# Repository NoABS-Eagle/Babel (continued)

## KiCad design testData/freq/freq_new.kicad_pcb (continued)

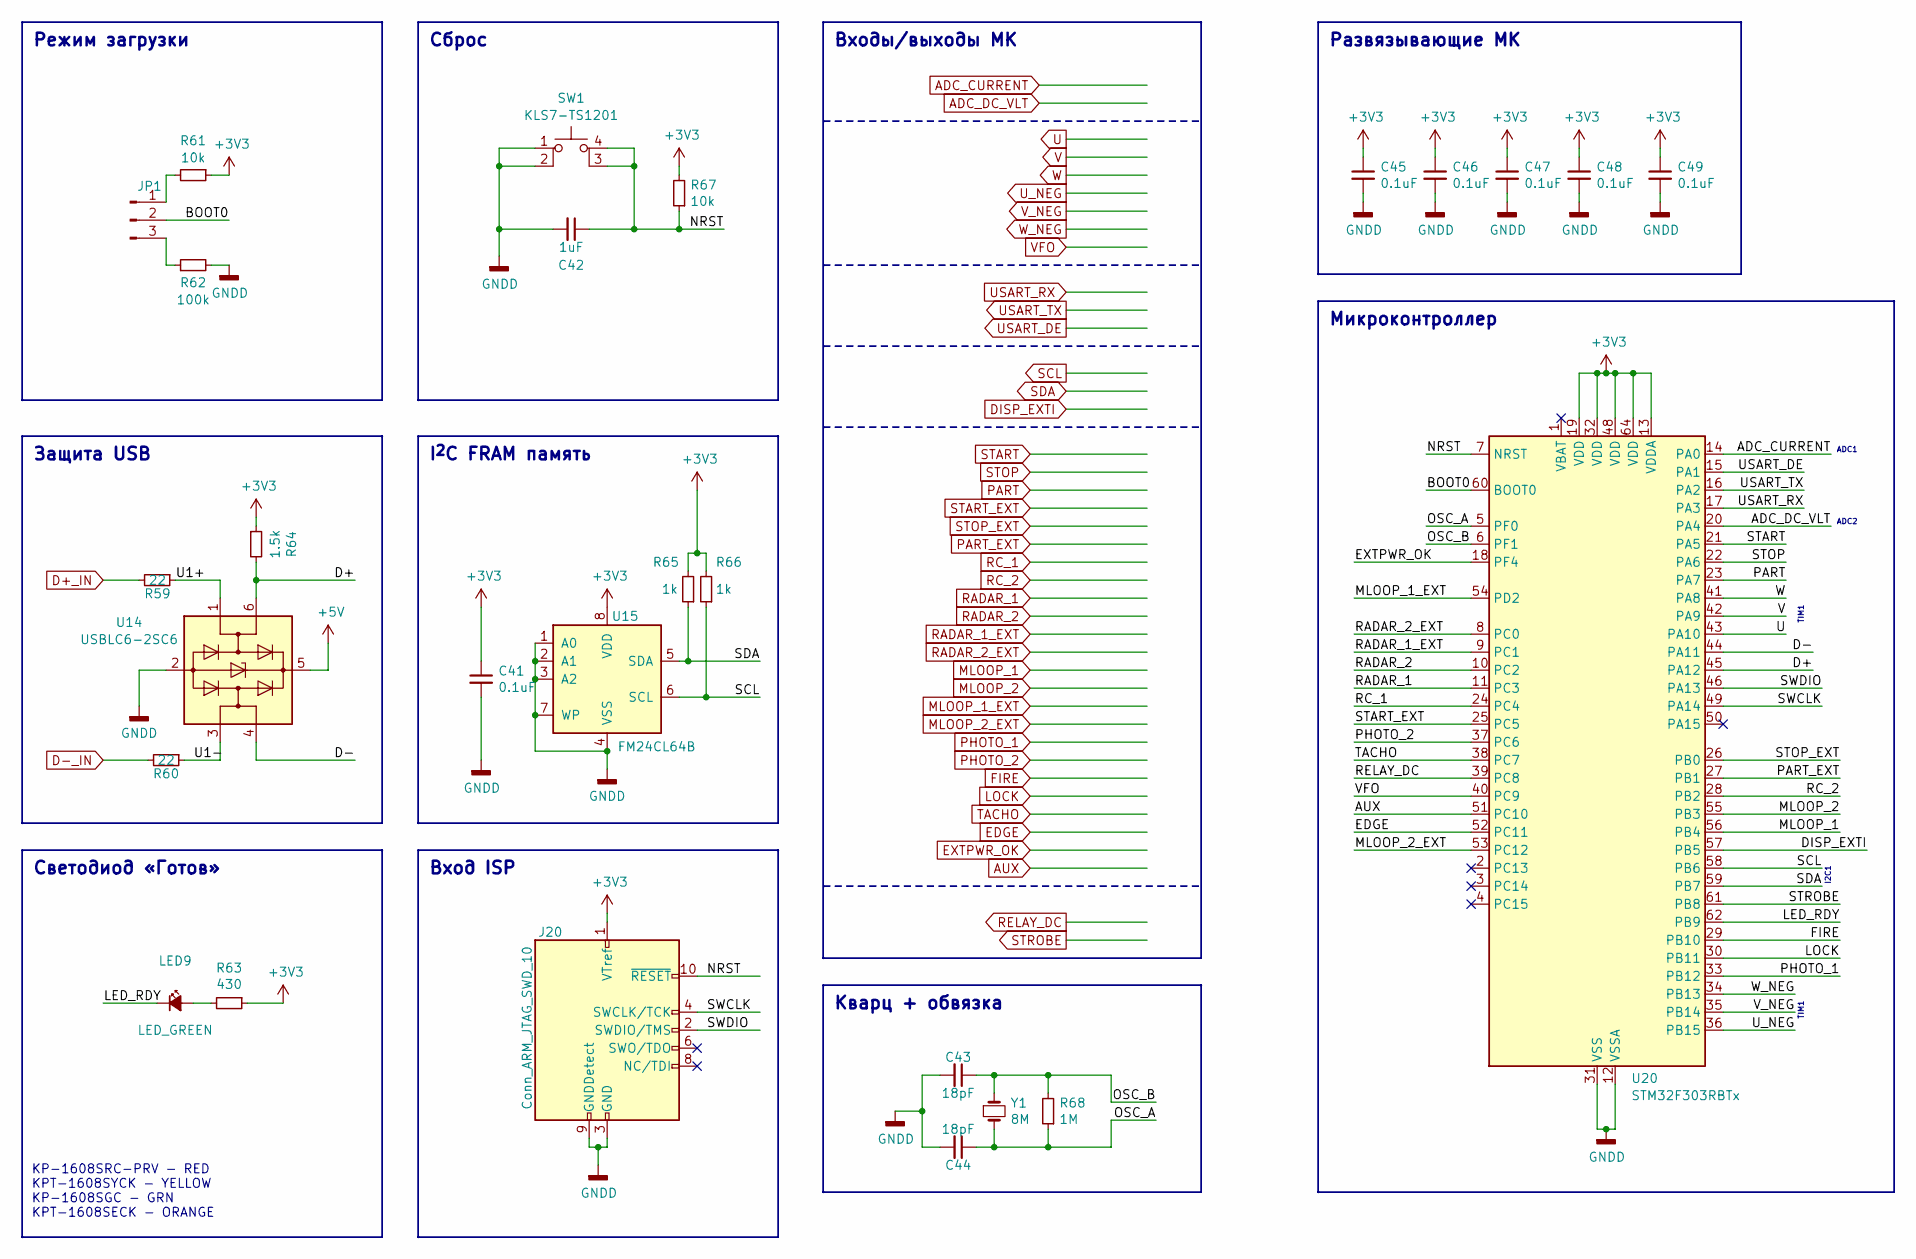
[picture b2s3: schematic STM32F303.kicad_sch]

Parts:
C41, C45, C46, C47, C48, C49: 0.1uF; C_0603_1608Metric
C42: 1uF; C_0603_1608Metric
C43, C44: 18pF; C_0603_1608Metric
J20: Conn_ARM_JTAG_SWD_10; PinHeader_2x05_P1.27mm_Vertical_SMD
JP1: Conn_01x03_Pin; PinHeader_1x03_P2.54mm_Vertical
LED9: LED_GREEN; LED_0603_1608Metric
R59, R60: 22; R_0603_1608Metric
R61, R67: 10k; R_0603_1608Metric
R62: 100k; R_0603_1608Metric
R63: 430; R_0603_1608Metric
R64: 1.5k; R_0603_1608Metric
R65, R66: 1k; R_0603_1608Metric
R68: 1M; R_0603_1608Metric
SW1: KLS7-TS1201
U14: USBLC6-2SC6; SOT-23-6
U15: FM24CL64B; SOIC-8_3.9x4.9mm_P1.27mm
U20: STM32F303RBTx; LQFP-64_10x10mm_P0.5mm
Y1: 8M; Crystal_SMD_HC49-SD

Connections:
+3V3: C41.1, C45.1, C46.1, C47.1, C48.1, C49.1, J20.1 (VTref), R61.1, R63.1, R64.1, R65.2, R66.2, R67.2, U15.8 (VDD), U20.13 (VDDA), U20.19 (VDD), U20.32 (VDD), U20.48 (VDD), U20.64 (VDD); also elsewhere on the board
+5V: U14.5 (VBUS); also elsewhere on the board
/MCU_SHEET/BOOT0: JP1.2, U20.60 (BOOT0)
/MCU_SHEET/D+: R64.2, U14.6 (I/O1), U20.45 (PA12)
/MCU_SHEET/D-: U14.4 (I/O2), U20.44 (PA11)
/MCU_SHEET/LED_RDY: LED9.1 (K), U20.62 (PB9)
/MCU_SHEET/NRST: C42.1, J20.10 (~RESET), R67.1, SW1.3 (K), SW1.4 (A), U20.7 (NRST)
/MCU_SHEET/OSC_A: C44.1, R68.1, U20.5 (PF0), Y1.2
/MCU_SHEET/OSC_B: C43.1, R68.2, U20.6 (PF1), Y1.1
/MCU_SHEET/SWCLK: J20.4 (SWCLK/TCK), U20.49 (PA14)
/MCU_SHEET/SWDIO: J20.2 (SWDIO/TMS), U20.46 (PA13)
/MCU_SHEET/U1+: R59.1, U14.1 (I/O1)
/MCU_SHEET/U1-: R60.1, U14.3 (I/O2)
ADC_CURRENT: U20.14 (PA0); also elsewhere on the board
ADC_DC_VLT: U20.20 (PA4); also elsewhere on the board
AUX: U20.51 (PC10); also elsewhere on the board
D+_IN: R59.2; also elsewhere on the board
D-_IN: R60.2; also elsewhere on the board
DISP_EXTI: U20.57 (PB5); also elsewhere on the board
EDGE: U20.52 (PC11); also elsewhere on the board
EXTPWR_OK: U20.18 (PF4); also elsewhere on the board
FIRE: U20.29 (PB10); also elsewhere on the board
GNDD: C41.2, C42.2, C43.2, C44.2, C45.2, C46.2, C47.2, C48.2, C49.2, J20.3 (GND), J20.5 (GND), J20.9 (GNDDetect), R62.2, SW1.1, SW1.2, U14.2 (GND), U15.1 (A0), U15.2 (A1), U15.3 (A2), U15.4 (VSS), U15.7 (WP), U20.12 (VSSA), U20.31 (VSS), U20.47 (VSS), U20.63 (VSS); also elsewhere on the board
LOCK: U20.30 (PB11); also elsewhere on the board
MLOOP_1: U20.56 (PB4); also elsewhere on the board
MLOOP_1_EXT: U20.54 (PD2); also elsewhere on the board
MLOOP_2: U20.55 (PB3); also elsewhere on the board
MLOOP_2_EXT: U20.53 (PC12); also elsewhere on the board
unnamed: JP1.1, R61.2
unnamed: JP1.3, R62.1
unnamed: LED9.2 (A), R63.2
PART: U20.23 (PA7); also elsewhere on the board
PART_EXT: U20.27 (PB1); also elsewhere on the board
PHOTO_1: U20.33 (PB12); also elsewhere on the board
PHOTO_2: U20.37 (PC6); also elsewhere on the board
RADAR_1: U20.11 (PC3); also elsewhere on the board
RADAR_1_EXT: U20.9 (PC1); also elsewhere on the board
RADAR_2: U20.10 (PC2); also elsewhere on the board
RADAR_2_EXT: U20.8 (PC0); also elsewhere on the board
RC_1: U20.24 (PC4); also elsewhere on the board
RC_2: U20.28 (PB2); also elsewhere on the board
RELAY_DC: U20.39 (PC8); also elsewhere on the board
SCL: R66.1, U15.6 (SCL), U20.58 (PB6); also elsewhere on the board
SDA: R65.1, U15.5 (SDA), U20.59 (PB7); also elsewhere on the board
START: U20.21 (PA5); also elsewhere on the board
START_EXT: U20.25 (PC5); also elsewhere on the board
STOP: U20.22 (PA6); also elsewhere on the board
STOP_EXT: U20.26 (PB0); also elsewhere on the board
STROBE: U20.61 (PB8); also elsewhere on the board
TACHO: U20.38 (PC7); also elsewhere on the board
U: U20.43 (PA10); also elsewhere on the board
USART_DE: U20.15 (PA1); also elsewhere on the board
USART_RX: U20.17 (PA3); also elsewhere on the board
USART_TX: U20.16 (PA2); also elsewhere on the board
U_NEG: U20.36 (PB15); also elsewhere on the board
V: U20.42 (PA9); also elsewhere on the board
VFO: U20.40 (PC9); also elsewhere on the board
V_NEG: U20.35 (PB14); also elsewhere on the board
W: U20.41 (PA8); also elsewhere on the board
W_NEG: U20.34 (PB13); also elsewhere on the board

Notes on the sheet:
Сброс
Вход ISP
Входы/выходы МК
Режим загрузки
Светодиод «Готов»
Микроконтроллер
Защита USB
Кварц + обвязка
Развязывающие МК
I^{2}C FRAM память
TIM1
KP-1608SRC-PRV - RED KPT-1608SYCK - YELLOW KP-1608SGC - GRN KPT-1608SECK - ORANGE
I2C1
ADC1
ADC2

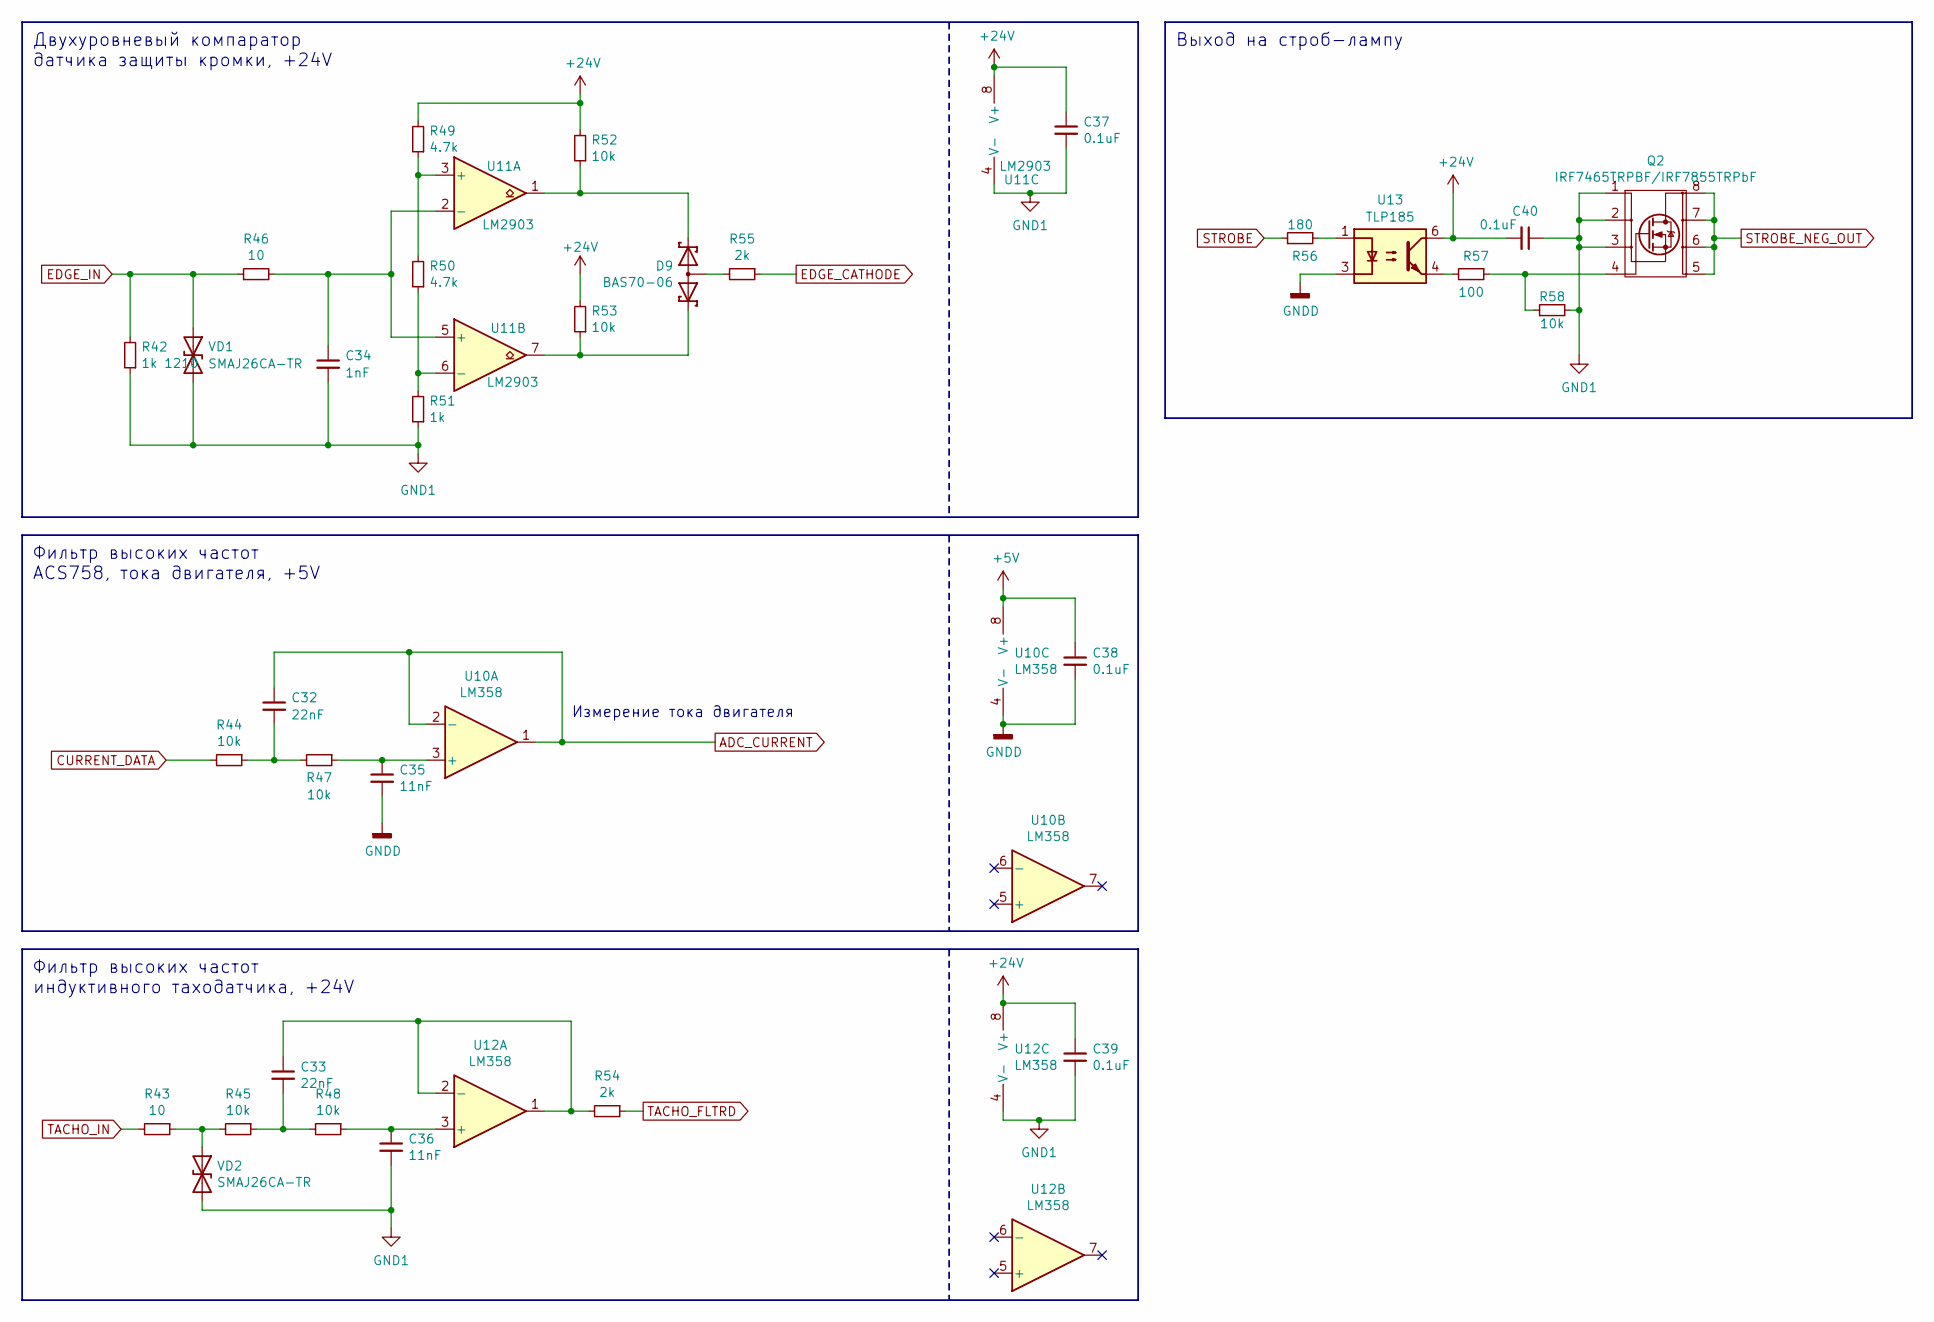
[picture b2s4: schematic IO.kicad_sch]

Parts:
C32, C33: 22nF; C_0603_1608Metric
C34: 1nF; C_0603_1608Metric
C35, C36: 11nF; C_0603_1608Metric
C37, C38, C39, C40: 0.1uF; C_0603_1608Metric
D9: BAS70-06; SOT23
Q2: IRF7465TRPBF/IRF7855TRPbF; SOIC-8_3.9x4.9mm_P1.27mm
R42: 1k 1210; R_1210_3225Metric
R43, R46: 10; R_0603_1608Metric
R44, R45, R47, R48, R52, R53, R58: 10k; R_0603_1608Metric
R49, R50: 4.7k; R_0603_1608Metric
R51: 1k; R_0603_1608Metric
R54, R55: 2k; R_0603_1608Metric
R56: 180; R_0603_1608Metric
R57: 100; R_0603_1608Metric
U10, U12: LM358; SOIC-8_3.9x4.9mm_P1.27mm
U11: LM2903; SOIC-8_3.9x4.9mm_P1.27mm
U13: TLP185; SOIC-4_4.55x3.7mm_P2.54mm
VD1, VD2: SMAJ26CA-TR; D_SMA

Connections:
24_EXT_NEG_IN: C34.2, C36.2, C37.2, C39.2, C40.1, Q2.1 (S), Q2.2 (S), Q2.3 (S), R42.1, R51.1, R58.2, U11.4 (V-), U12.4 (V-), VD1.2 (A2), VD2.2 (A2); also elsewhere on the board
+5V: C38.1, U10.8 (V+); also elsewhere on the board
+24V: C37.1, C39.1, C40.2, R49.2, R52.2, R53.2, U11.8 (V+), U12.8 (V+), U13.6; also elsewhere on the board
ADC_CURRENT: C32.1, U10.1, U10.2 (-); also elsewhere on the board
CURRENT_DATA: R44.2; also elsewhere on the board
EDGE_CATHODE: R55.1; also elsewhere on the board
EDGE_IN: R42.2, R46.1, VD1.1 (A1); also elsewhere on the board
GNDD: C35.2, C38.2, U10.4 (V-), U13.3; also elsewhere on the board
unnamed: C32.2, R44.1, R47.2
unnamed: C33.2, R45.1, R48.2
unnamed: D9.1, R52.1, U11.1
unnamed: D9.2, R53.1, U11.7
unnamed: D9.3, R55.2
unnamed: Q2.4 (G), R57.1, R58.1
unnamed: R56.2, U13.1
unnamed: R57.2, U13.4
unnamed: C35.1, R47.1, U10.3 (+)
unnamed: R49.1, R50.2, U11.3 (+)
unnamed: C34.1, R46.2, U11.2 (-), U11.5 (+)
unnamed: R50.1, R51.2, U11.6 (-)
unnamed: C36.1, R48.1, U12.3 (+)
unnamed: C33.1, R54.2, U12.1, U12.2 (-)
unnamed: R43.1, R45.2, VD2.1 (A1)
STROBE: R56.1; also elsewhere on the board
STROBE_NEG_OUT: Q2.5 (D), Q2.6 (D), Q2.7 (D), Q2.8 (D); also elsewhere on the board
TACHO_FLTRD: R54.1; also elsewhere on the board
TACHO_IN: R43.2; also elsewhere on the board

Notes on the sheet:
Двухуровневый компаратор датчика защиты кромки, +24V
Выход на строб-лампу
Фильтр высоких частот индуктивного таходатчика, +24V
Фильтр высоких частот ACS758, тока двигателя, +5V
Измерение тока двигателя

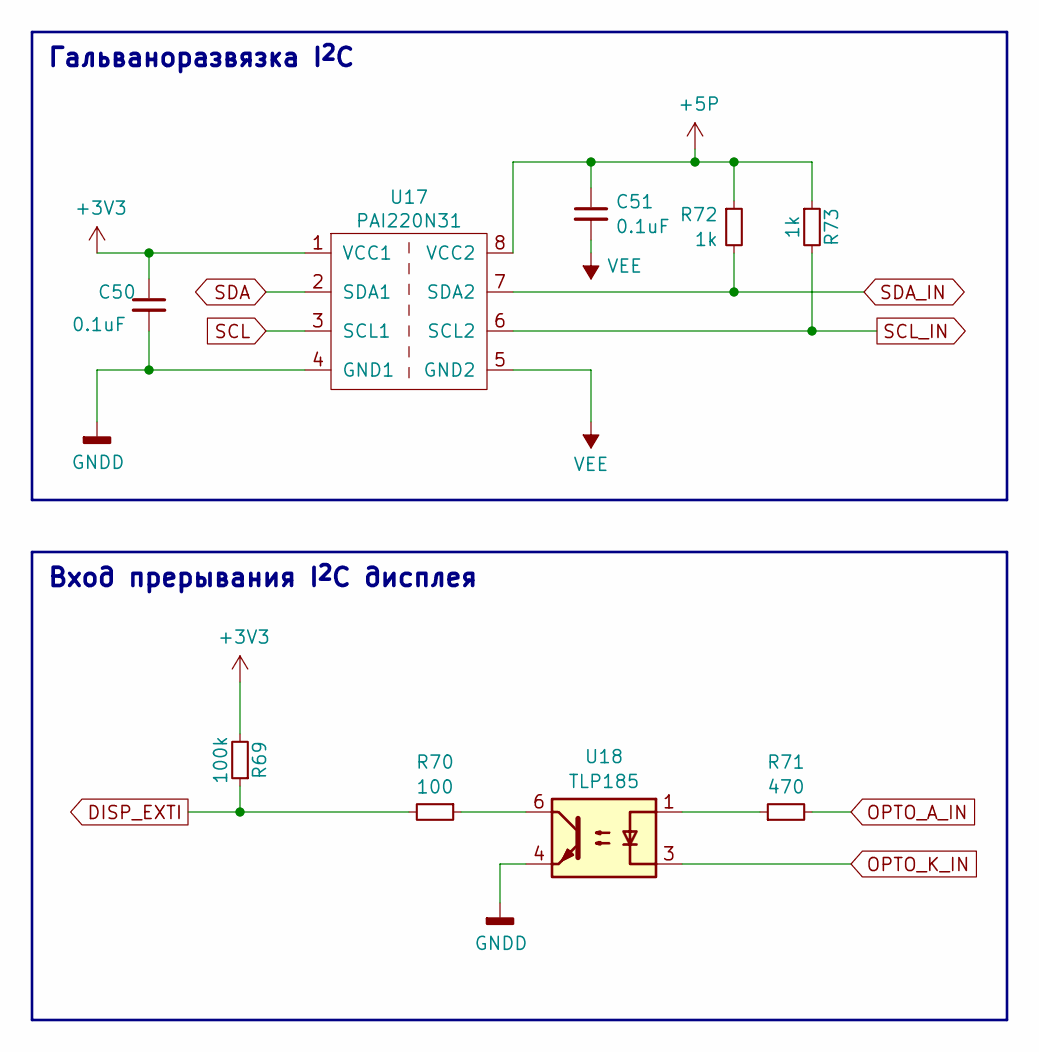
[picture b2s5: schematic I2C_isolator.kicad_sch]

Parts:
C50, C51: 0.1uF; C_0603_1608Metric
R69: 100k; R_0603_1608Metric
R70: 100; R_0603_1608Metric
R71: 470; R_0603_1608Metric
R72, R73: 1k; R_0603_1608Metric
U17: PAI220N31; SOIC127P599X175-8N
U18: TLP185; SOIC-4_4.55x3.7mm_P2.54mm

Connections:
+3V3: C50.1, R69.2, U17.1 (VCC1); also elsewhere on the board
+5P: C51.1, R72.1, R73.1, U17.8 (VCC2); also elsewhere on the board
DISP_EXTI: R69.1, R70.2; also elsewhere on the board
GNDD: C50.2, U17.4 (GND1), U18.4; also elsewhere on the board
unnamed: R70.1, U18.6
unnamed: R71.1, U18.1
OPTO_A_IN: R71.2; also elsewhere on the board
OPTO_K_IN: U18.3; also elsewhere on the board
SCL: U17.3 (SCL1); also elsewhere on the board
SCL_IN: R73.2, U17.6 (SCL2); also elsewhere on the board
SDA: U17.2 (SDA1); also elsewhere on the board
SDA_IN: R72.2, U17.7 (SDA2); also elsewhere on the board
VEE: C51.2, U17.5 (GND2); also elsewhere on the board

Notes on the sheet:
Гальваноразвязка I^{2}C
Вход прерывания I^{2}C дисплея

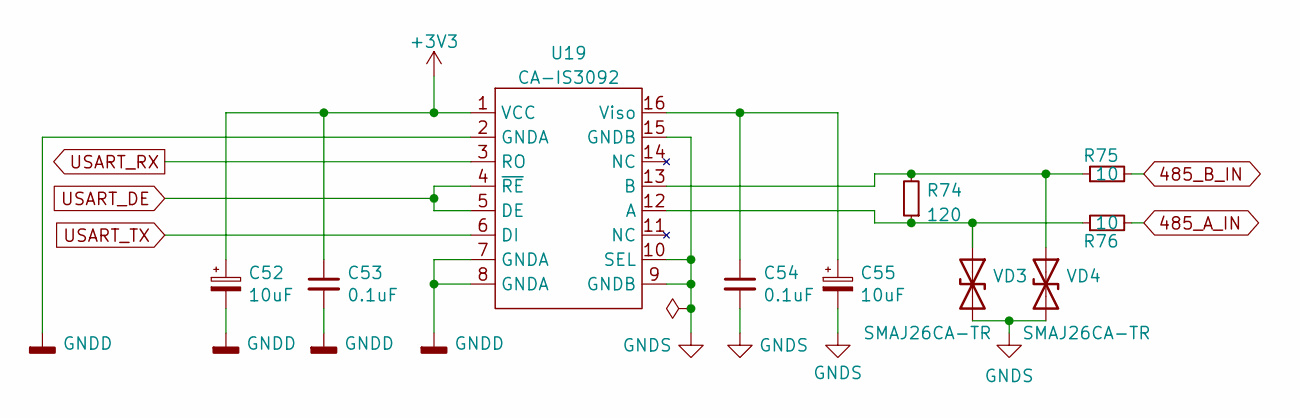
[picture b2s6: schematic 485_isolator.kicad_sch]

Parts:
C52, C55: 10uF; CP_Elec_4x5.3
C53, C54: 0.1uF; C_0603_1608Metric
R74: 120; R_0603_1608Metric
R75, R76: 10; R_0603_1608Metric
U19: CA-IS3092; SOIC-16W_7.5x10.3mm_P1.27mm
VD3, VD4: SMAJ26CA-TR; D_SMA

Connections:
485_A_IN: R76.2; also elsewhere on the board
485_B_IN: R75.2; also elsewhere on the board
+3V3: C52.1, C53.1, U19.1 (VCC); also elsewhere on the board
GNDD: C52.2, C53.2, U19.2 (GNDA), U19.7 (GNDA), U19.8 (GNDA); also elsewhere on the board
GNDS: C54.2, C55.2, U19.9 (GNDB), U19.10 (SEL), U19.15 (GNDB), VD3.2 (A2), VD4.2 (A2)
unnamed: R74.1, R76.1, U19.12 (A), VD3.1 (A1)
unnamed: R74.2, R75.1, U19.13 (B), VD4.1 (A1)
unnamed: C54.1, C55.1, U19.16 (Viso)
USART_DE: U19.4 (~RE), U19.5 (DE); also elsewhere on the board
USART_RX: U19.3 (RO); also elsewhere on the board
USART_TX: U19.6 (DI); also elsewhere on the board

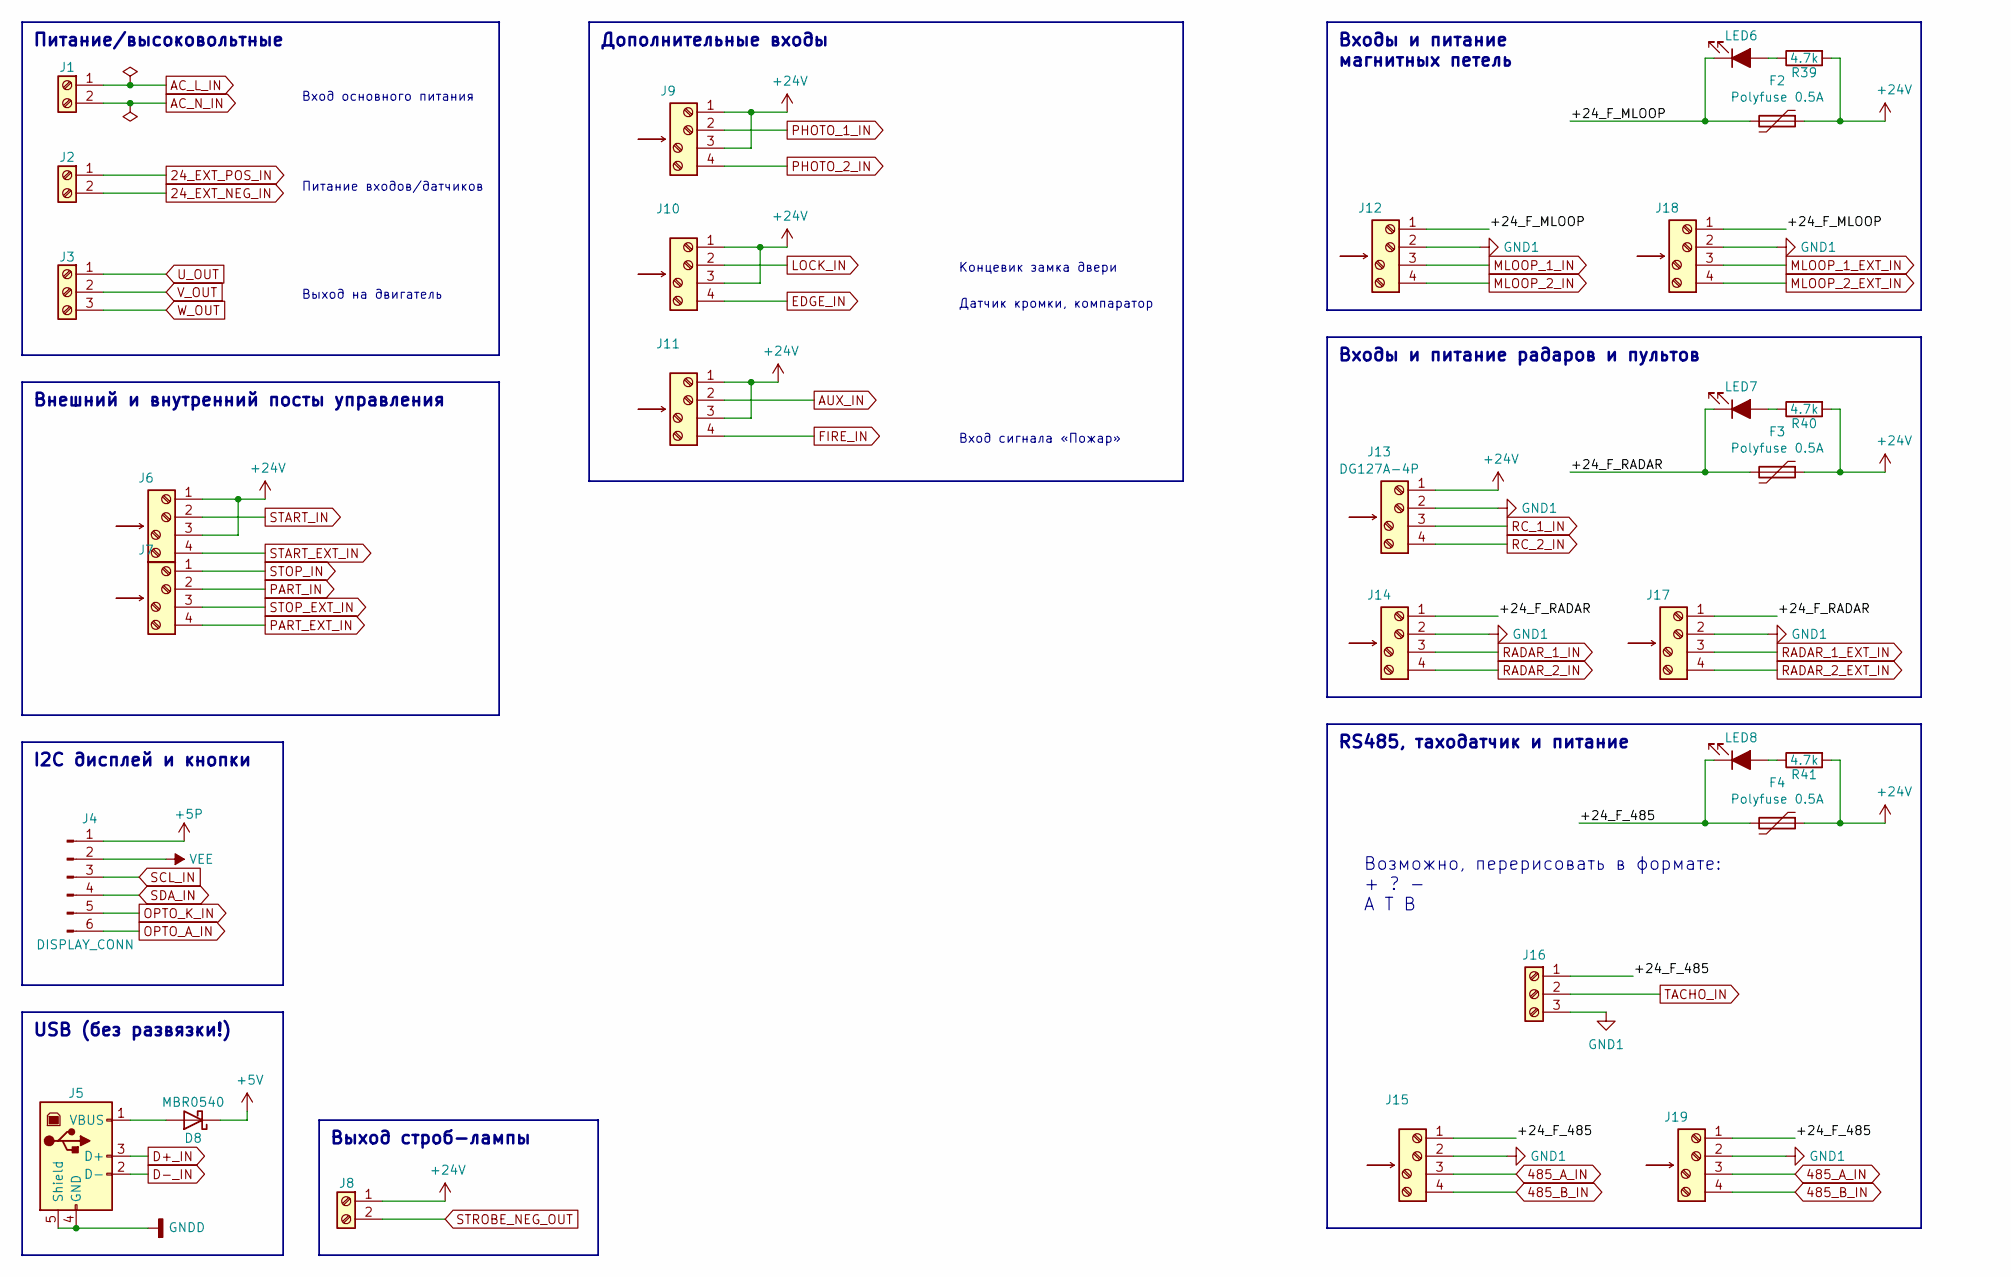
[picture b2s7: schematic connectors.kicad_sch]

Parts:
D8: MBR0540; D_SOD-123
F2, F3, F4: Polyfuse 0.5A; Fuse_1812_4532Metric
J1, J2: Screw_Terminal_01x02; TerminalBlock_MetzConnect_Type171_RT13702HBWC_1x02_P7.50mm_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
J3: Screw_Terminal_01x03; TerminalBlock_MetzConnect_Type171_RT13703HBWC_1x03_P7.50mm_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
J4: DISPLAY_CONN; IDC-Header_2x03_P2.54mm_Vertical
J5: USB_B; USB_B_OST_USB-B1HSxx_Horizontal
J6, J7, J9, J10, J11, J12, J13, J14, J15, J17, J18, J19: DG127A-4P
J8: Screw_Terminal_01x02; TerminalBlock_Phoenix_PT-1,5-2-5.0-H_1x02_P5.00mm_Horizontal
J16: Screw_Terminal_01x03; TerminalBlock_Phoenix_PT-1,5-3-5.0-H_1x03_P5.00mm_Horizontal
LED6, LED7, LED8: LED_RED; LED_0603_1608Metric
R39, R40, R41: 4.7k; R_0603_1608Metric

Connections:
24_EXT_NEG_IN: J2.2, J12.2, J13.2, J14.2, J15.2, J16.3, J17.2, J18.2, J19.2; also elsewhere on the board
24_EXT_POS_IN: J2.1; also elsewhere on the board
485_A_IN: J15.3, J19.3; also elsewhere on the board
485_B_IN: J15.4, J19.4; also elsewhere on the board
+5P: J4.1; also elsewhere on the board
+5V: D8.1 (K); also elsewhere on the board
+24V: F2.1, F3.1, F4.1, J6.1, J6.3, J8.1, J9.1, J9.3, J10.1, J10.3, J11.1, J11.3, J13.1, R39.2, R40.2, R41.2; also elsewhere on the board
/Connectors/+24_F_485: F4.2, J15.1, J16.1, J19.1, LED8.1 (K)
/Connectors/+24_F_MLOOP: F2.2, J12.1, J18.1, LED6.1 (K)
/Connectors/+24_F_RADAR: F3.2, J14.1, J17.1, LED7.1 (K)
AC_L_IN: J1.1; also elsewhere on the board
AC_N_IN: J1.2; also elsewhere on the board
AUX_IN: J11.2; also elsewhere on the board
D+_IN: J5.3 (D+); also elsewhere on the board
D-_IN: J5.2 (D-); also elsewhere on the board
EDGE_IN: J10.4; also elsewhere on the board
FIRE_IN: J11.4; also elsewhere on the board
GNDD: J5.4 (GND), J5.5 (Shield); also elsewhere on the board
LOCK_IN: J10.2; also elsewhere on the board
MLOOP_1_EXT_IN: J18.3; also elsewhere on the board
MLOOP_1_IN: J12.3; also elsewhere on the board
MLOOP_2_EXT_IN: J18.4; also elsewhere on the board
MLOOP_2_IN: J12.4; also elsewhere on the board
unnamed: D8.2 (A), J5.1 (VBUS)
unnamed: LED6.2 (A), R39.1
unnamed: LED7.2 (A), R40.1
unnamed: LED8.2 (A), R41.1
OPTO_A_IN: J4.6; also elsewhere on the board
OPTO_K_IN: J4.5; also elsewhere on the board
PART_EXT_IN: J7.4; also elsewhere on the board
PART_IN: J7.2; also elsewhere on the board
PHOTO_1_IN: J9.2; also elsewhere on the board
PHOTO_2_IN: J9.4; also elsewhere on the board
RADAR_1_EXT_IN: J17.3; also elsewhere on the board
RADAR_1_IN: J14.3; also elsewhere on the board
RADAR_2_EXT_IN: J17.4; also elsewhere on the board
RADAR_2_IN: J14.4; also elsewhere on the board
RC_1_IN: J13.3; also elsewhere on the board
RC_2_IN: J13.4; also elsewhere on the board
SCL_IN: J4.3; also elsewhere on the board
SDA_IN: J4.4; also elsewhere on the board
START_EXT_IN: J6.4; also elsewhere on the board
START_IN: J6.2; also elsewhere on the board
STOP_EXT_IN: J7.3; also elsewhere on the board
STOP_IN: J7.1; also elsewhere on the board
STROBE_NEG_OUT: J8.2; also elsewhere on the board
TACHO_IN: J16.2; also elsewhere on the board
U_OUT: J3.1; also elsewhere on the board
VEE: J4.2; also elsewhere on the board
V_OUT: J3.2; also elsewhere on the board
W_OUT: J3.3; also elsewhere on the board

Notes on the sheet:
Входы и питание магнитных петель
RS485, таходатчик и питание
Входы и питание радаров и пультов
Питание/высоковольтные
Внешний и внутренний посты управления
Дополнительные входы
USB (без развязки!)
I2C дисплей и кнопки
Выход строб-лампы
Выход на двигатель
Датчик кромки, компаратор
Вход сигнала «Пожар»
Возможно, перерисовать в формате: + ? - A T B
Питание входов/датчиков
Вход основного питания
Концевик замка двери

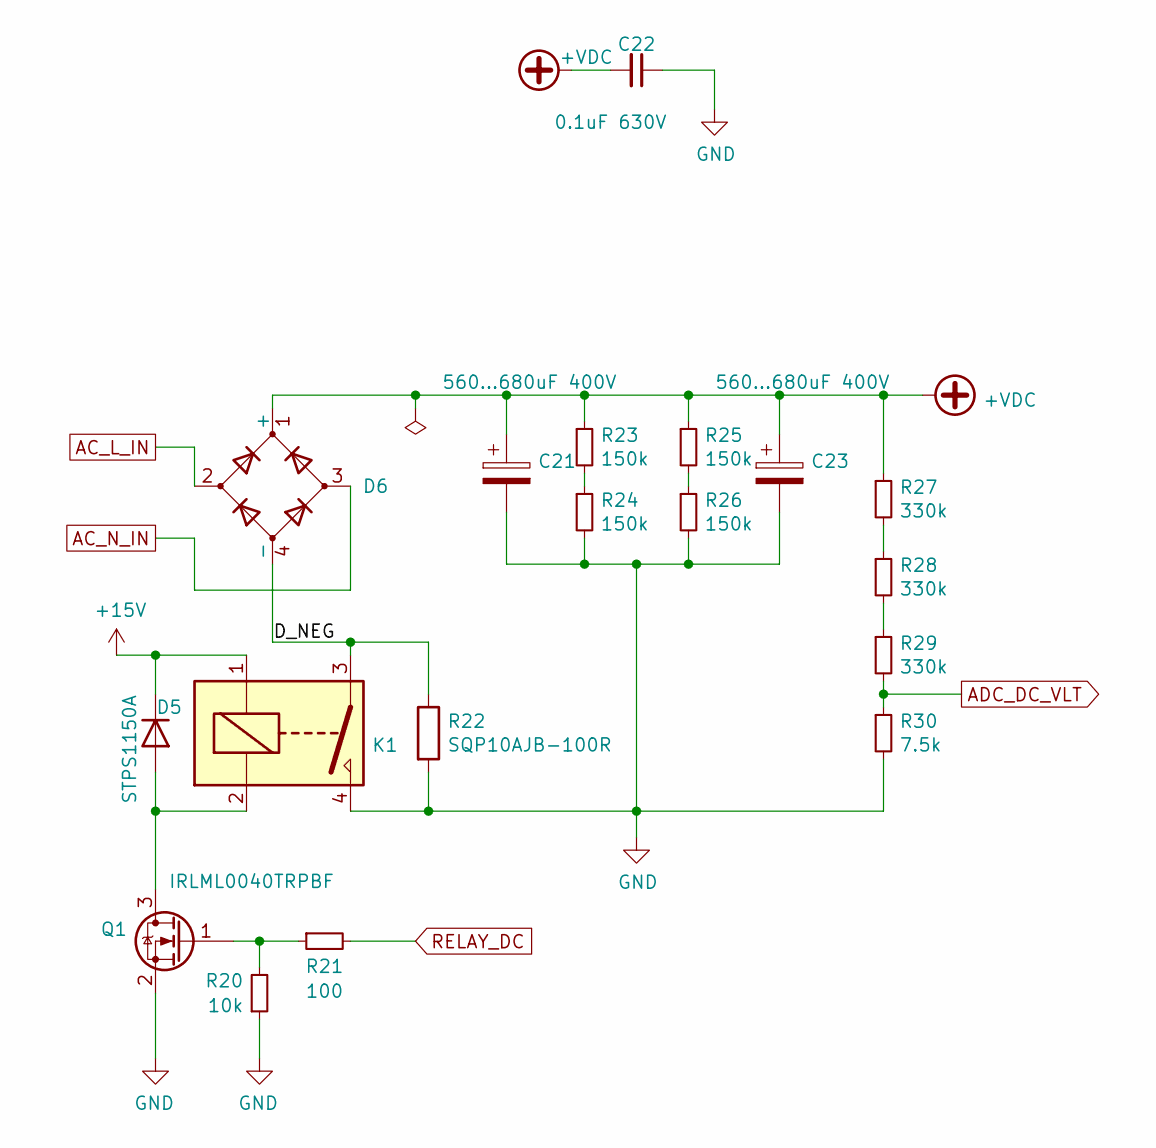
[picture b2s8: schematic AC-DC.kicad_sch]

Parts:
C21, C23: 560…680uF 400V; CP_Radial_D35.0mm_P10.00mm_SnapIn
C22: 0.1uF 630V; C_Rect_L13.0mm_W6.0mm_P10.00mm_FKS3_FKP3_MKS4
D5: STPS1150A; D_SMA
D6: GBJ2510-F
K1: G4A-1A-PE-12DC; G4A-1A-PE
Q1: IRLML0040TRPBF; SOT-23
R20: 10k; R_0603_1608Metric
R21: 100; R_0603_1608Metric
R22: SQP10AJB-100R
R23, R24, R25, R26: 150k; R_2010_5025Metric
R27, R28, R29: 330k; R_1206_3216Metric
R30: 7.5k; R_1206_3216Metric

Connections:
+15V: D5.1 (K), K1.1; also elsewhere on the board
+VDC: C21.1, C22.2, C23.1, D6.1 (+), R23.1, R25.1, R27.1; also elsewhere on the board
/AC-DC/D_NEG: D6.4 (-), K1.3, R22.1
AC_L_IN: D6.2; also elsewhere on the board
AC_N_IN: D6.3; also elsewhere on the board
ADC_DC_VLT: R29.2, R30.1; also elsewhere on the board
GND: C21.2, C22.1, C23.2, K1.4, Q1.2 (S), R20.1, R22.2, R24.2, R26.2, R30.2; also elsewhere on the board
unnamed: D5.2 (A), K1.2, Q1.3 (D)
unnamed: Q1.1 (G), R20.2, R21.1
unnamed: R23.2, R24.1
unnamed: R25.2, R26.1
unnamed: R27.2, R28.1
unnamed: R28.2, R29.1
RELAY_DC: R21.2; also elsewhere on the board

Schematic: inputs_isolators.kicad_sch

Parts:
U4, U5, U6, U7, U8, U9: SFH6916/PS2801-4-F3-A; SOIC127P686X203-16N
VS1, VS2, VS3, VS4, VS5, VS6, VS7, VS8, VS9, VS10, VS11, VS12, VS13, VS14, VS15, VS16, VS17, VS18, VS19, VS20, VS21: NSI45020AT1G; D_SOD-123

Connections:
24_EXT_NEG_IN: U4.2, U4.4, U4.6, U4.8, U5.2, U5.4, U5.6, U5.8, U6.2, U6.4, U6.6, U6.8, U7.2, U7.4, U7.6, U7.8, U8.2, U8.4, U8.6, U8.8, U9.2, U9.6, U9.8; also elsewhere on the board
+24V: U9.3, VS21.2 (A); also elsewhere on the board
AUX: U9.10; also elsewhere on the board
AUX_IN: U9.7; also elsewhere on the board
EDGE: U9.14; also elsewhere on the board
EDGE_CATHODE: U9.4; also elsewhere on the board
EXTPWR_OK: U9.12; also elsewhere on the board
FIRE: U6.16; also elsewhere on the board
FIRE_IN: VS9.2 (A); also elsewhere on the board
GNDD: U4.9, U4.11, U4.13, U4.15, U5.9, U5.11, U5.13, U5.15, U6.9, U6.11, U6.13, U6.15, U7.9, U7.11, U7.13, U7.15, U8.9, U8.11, U8.13, U8.15, U9.9, U9.11, U9.13, U9.15; also elsewhere on the board
LOCK: U6.14; also elsewhere on the board
LOCK_IN: VS10.2 (A); also elsewhere on the board
MLOOP_1: U8.16; also elsewhere on the board
MLOOP_1_EXT: U8.12; also elsewhere on the board
MLOOP_1_EXT_IN: VS19.2 (A); also elsewhere on the board
MLOOP_1_IN: VS17.2 (A); also elsewhere on the board
MLOOP_2: U8.14; also elsewhere on the board
MLOOP_2_EXT: U8.10; also elsewhere on the board
MLOOP_2_EXT_IN: VS20.2 (A); also elsewhere on the board
MLOOP_2_IN: VS18.2 (A); also elsewhere on the board
unnamed: U4.1, VS1.1 (C)
unnamed: U4.3, VS2.1 (C)
unnamed: U4.5, VS3.1 (C)
unnamed: U4.7, VS4.1 (C)
unnamed: U5.1, VS5.1 (C)
unnamed: U5.3, VS6.1 (C)
unnamed: U5.5, VS7.1 (C)
unnamed: U5.7, VS8.1 (C)
unnamed: U6.1, VS9.1 (C)
unnamed: U6.3, VS10.1 (C)
unnamed: U6.5, VS11.1 (C)
unnamed: U6.7, VS12.1 (C)
unnamed: U7.1, VS13.1 (C)
unnamed: U7.3, VS14.1 (C)
unnamed: U7.5, VS15.1 (C)
unnamed: U7.7, VS16.1 (C)
unnamed: U8.1, VS17.1 (C)
unnamed: U8.3, VS18.1 (C)
unnamed: U8.5, VS19.1 (C)
unnamed: U8.7, VS20.1 (C)
unnamed: U9.5, VS21.1 (C)
PART: U7.12; also elsewhere on the board
PART_EXT: U4.12; also elsewhere on the board
PART_EXT_IN: VS3.2 (A); also elsewhere on the board
PART_IN: VS15.2 (A); also elsewhere on the board
PHOTO_1: U6.12; also elsewhere on the board
PHOTO_1_IN: VS11.2 (A); also elsewhere on the board
PHOTO_2: U6.10; also elsewhere on the board
PHOTO_2_IN: VS12.2 (A); also elsewhere on the board
RADAR_1: U5.16; also elsewhere on the board
RADAR_1_EXT: U5.12; also elsewhere on the board
RADAR_1_EXT_IN: VS7.2 (A); also elsewhere on the board
RADAR_1_IN: VS5.2 (A); also elsewhere on the board
RADAR_2: U5.14; also elsewhere on the board
RADAR_2_EXT: U5.10; also elsewhere on the board
RADAR_2_EXT_IN: VS8.2 (A); also elsewhere on the board
RADAR_2_IN: VS6.2 (A); also elsewhere on the board
RC_1: U7.10; also elsewhere on the board
RC_1_IN: VS16.2 (A); also elsewhere on the board
RC_2: U4.10; also elsewhere on the board
RC_2_IN: VS4.2 (A); also elsewhere on the board
START: U7.16; also elsewhere on the board
START_EXT: U4.16; also elsewhere on the board
START_EXT_IN: VS1.2 (A); also elsewhere on the board
START_IN: VS13.2 (A); also elsewhere on the board
STOP: U7.14; also elsewhere on the board
STOP_EXT: U4.14; also elsewhere on the board
STOP_EXT_IN: VS2.2 (A); also elsewhere on the board
STOP_IN: VS14.2 (A); also elsewhere on the board
TACHO: U9.16; also elsewhere on the board
TACHO_FLTRD: U9.1; also elsewhere on the board

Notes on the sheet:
Датчик кромки, выход компаратора
Концевик замка двери

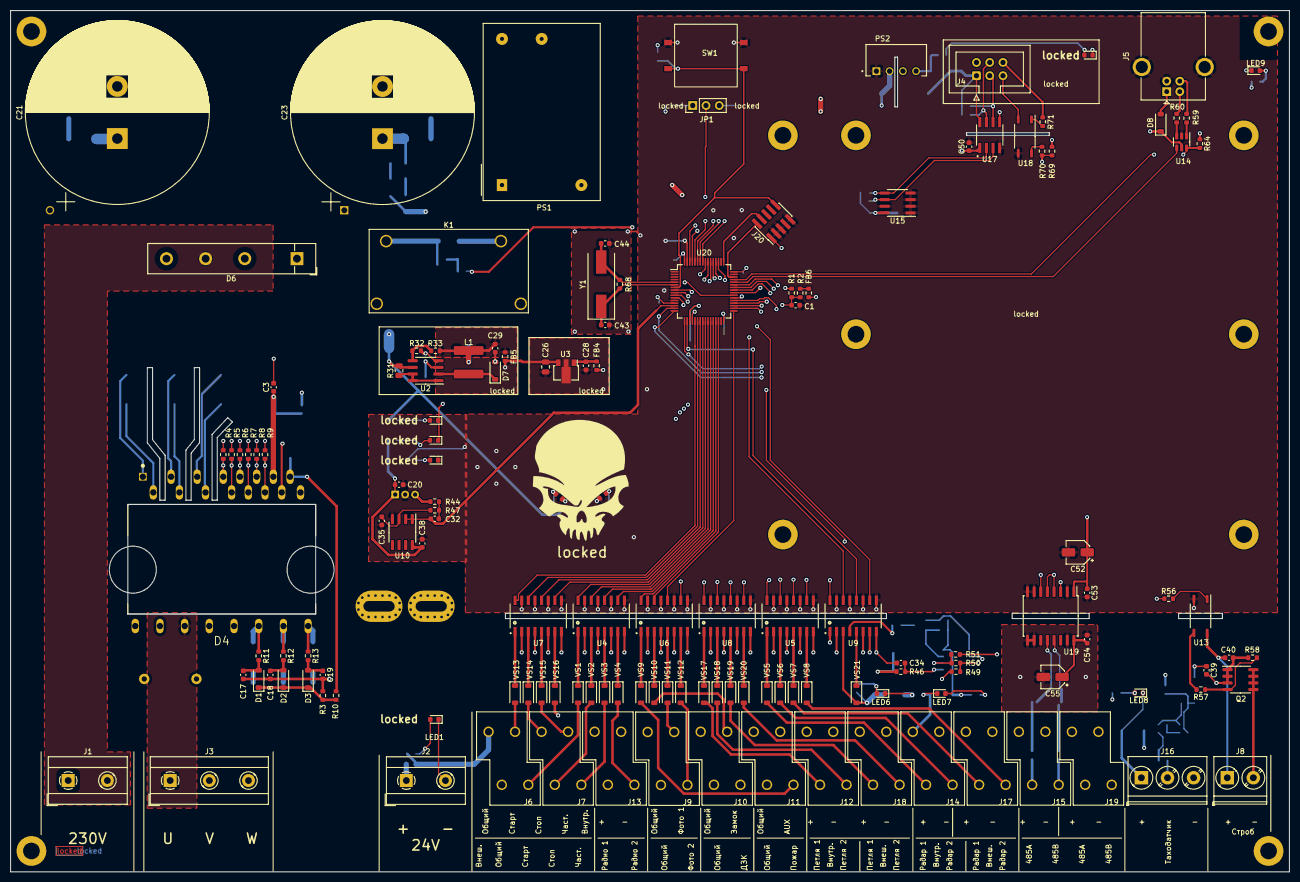
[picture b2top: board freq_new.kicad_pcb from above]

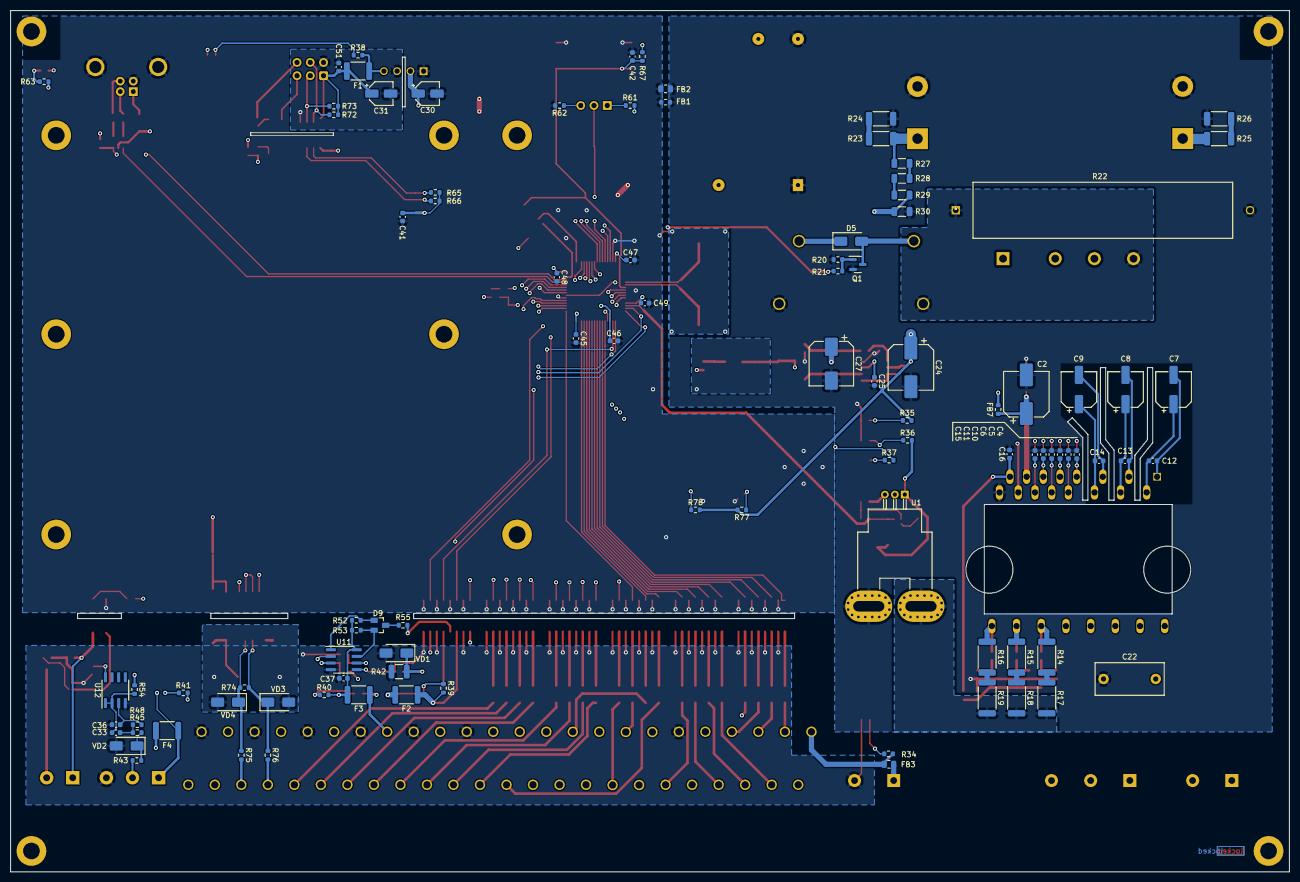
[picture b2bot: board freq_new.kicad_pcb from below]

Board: 4 copper layers, 245.0 x 165.0 mm, 248 parts (95 on the bottom side), 203 nets.

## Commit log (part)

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2026-06-20 Add Babel converter: Eagle/Altium/KiCad <-> IR pipeline
    First commit of the actual project code (babel/ package was never
    tracked before). Includes Eagle<->IR, Altium<->IR, IR->KiCad converters,
    SVG renderer, Flask viewer app, design docs, and test fixtures.
    Adds .gitignore for runtime session cache, CDN-downloaded 3D viewer
    assets, a third-party installer binary, generated exporter output,
    and Eagle's own editor backup files - none of which belong in version
